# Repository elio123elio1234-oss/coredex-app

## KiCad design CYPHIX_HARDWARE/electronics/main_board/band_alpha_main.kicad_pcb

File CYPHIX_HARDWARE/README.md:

# CYPHIX_HARDWARE — Band α hardware design

The product hardware for **CYPHIX Band α**: the wearable 6-lead ECG strap with
dry electrodes that replaces the ESP32 + ADS1293 prototype. Requirements come
from the Band α specification (the bilingual artifact page,
`claude.ai/artifact/PpmwYJec8DWmWGM8rhy5re`).

The plan is built from the **product**: `system/product_tree.py` lists every deliverable, every
interface between two parts and every specification requirement with how it is proven, and its check
fails on an incomplete row. Risks are still tested in the cheapest way that can prove them, and the next
stage is paid for only after the previous one passes. (Until v0.16.0 the plan was built from risks alone,
and whole parts fell through it: the strap flex, the test plan, the board's fit in the housing.) The plan, with its live progress log, is the Hebrew page
published from `plan/plan.html`
(`claude.ai/artifact/PyT22bDzE1Ed9x9vdyoaew`).

## Stages

| # | Stage | Proves | Cost |
|---|---|---|---|
| 0 | On the computer | the design closes: size from the parts, schematic, parts available, everything fits in a solid model | none |
| 1 | Dry pads on the existing prototype | steel pads at the planned size give a readable ECG | about none |
| 2 | The new chip on the bench | the ADS129x family, the 4-channel plan and the existing apps work together | about none: the TI ADS1298 board is already owned |
| 3 | First wearable | miniature board, housing, strap and the flex inside it work on a wrist | being recomputed: the old $800–1,500 for five left out custom steel, sapphire, ceramic, the strap mould and the dock |
| 4 | Fixes and safety | safe and stable enough for a hospital study | $800–1,500 plus an accredited lab |

## Layout

```
CYPHIX_HARDWARE/
├── plan/          the plan page (plan.html + img/); publish plan.html to update the page
├── system/        product_tree.py: every deliverable, interface and requirement check (tree_html.py puts it on the plan page);
│                  budget.py → BUDGET.md: size, battery and mass, computed bottom-up from the parts
├── mechanical/    band_id.py = the industrial design model, concept v3.2 (render_v32.py + studio/ make its pictures,
│                  render_id.py the v3.1 ones; export_web_id.py feeds the page's 3D viewer); band_premium.py = the premium side variant P1, DROPPED by the owner
│                  2026-11-15 and off the page (code kept for reference only; its render/export scripts are not part of the page)
│                  (render_p.py, export_web_p.py); band_alpha.py = the first packaging check
├── electronics/   DESIGN_INTENT.md (the brief) + main_board/: schematic + 6-layer board rev 0.1 (make_schematic.py, make_pcb.py --route → KiCad 10 + Freerouting; DESIGN_NOTES.md, TEST_PLAN.md, bom.csv, PDF) + strap_flex/ (the RA flex); autorouted, not reviewed
├── firmware/      stage2_ads129x_xiao/: the bench firmware (XIAO nRF52840 + TI ADS1298 board)
├── experiments/   step-by-step protocols for the tests a person has to run
└── tools/         helper scripts
```

`HW_PLAYGROUND/` (the ADS1293 research area) stays as it is and is read-only
from here.

## Rules that are specific to this folder

- **No size is an input.** The render (35 × 26 × ~6 mm) and the spec's MEC-01
  (45 × 30 × 12 mm) were not derived from the parts. `system/budget.py` is the
  one place the module size comes from; the CAD model imports it.
- **The apps stay frozen at 320 Hz until the hardware is proven.** Stage 2
  firmware has a compatibility mode that streams the existing packet format, so
  no app change is needed to test new hardware. Moving the apps to 4 channels
  and 500 SPS is a `CYPHIX_SHARED` change and needs the owner's approval.
- **Patient safety is designed in from the first schematic**: patient current
  limited by series resistance, no recording while charging, battery-only
  operation whenever electrodes are on a person.
- **Nothing here has been measured until a stage says so.** A clean ERC/DRC, a
  collision-free model and a compiling firmware prove the design is
  well-formed, not that it works.
- A person with electronics experience reviews every board before it is ordered.
- **A stage starts only when the product tree has nothing `missing` or `conflict` that the stage needs**,
  and an independent reviewer (someone who did not write the design) has been through every file.

## Tools

- Python 3.12 in `.venv/` (`requirements.txt`): CadQuery for solids and STEP,
  PyVista for the pictures.
- KiCad 10 installed per user at
  `%LOCALAPPDATA%\Programs\KiCad\10.0` (`bin\kicad-cli.exe`).
- PlatformIO at `%USERPROFILE%\.platformio\penv\Scripts\pio.exe`.

<!-- v0.16.0 — the plan is built from the product tree (system/product_tree.py); stage-3 cost withdrawn; stage gate rule; earlier: what the folder is, its stages, layout (concept v3.2) and rules -->

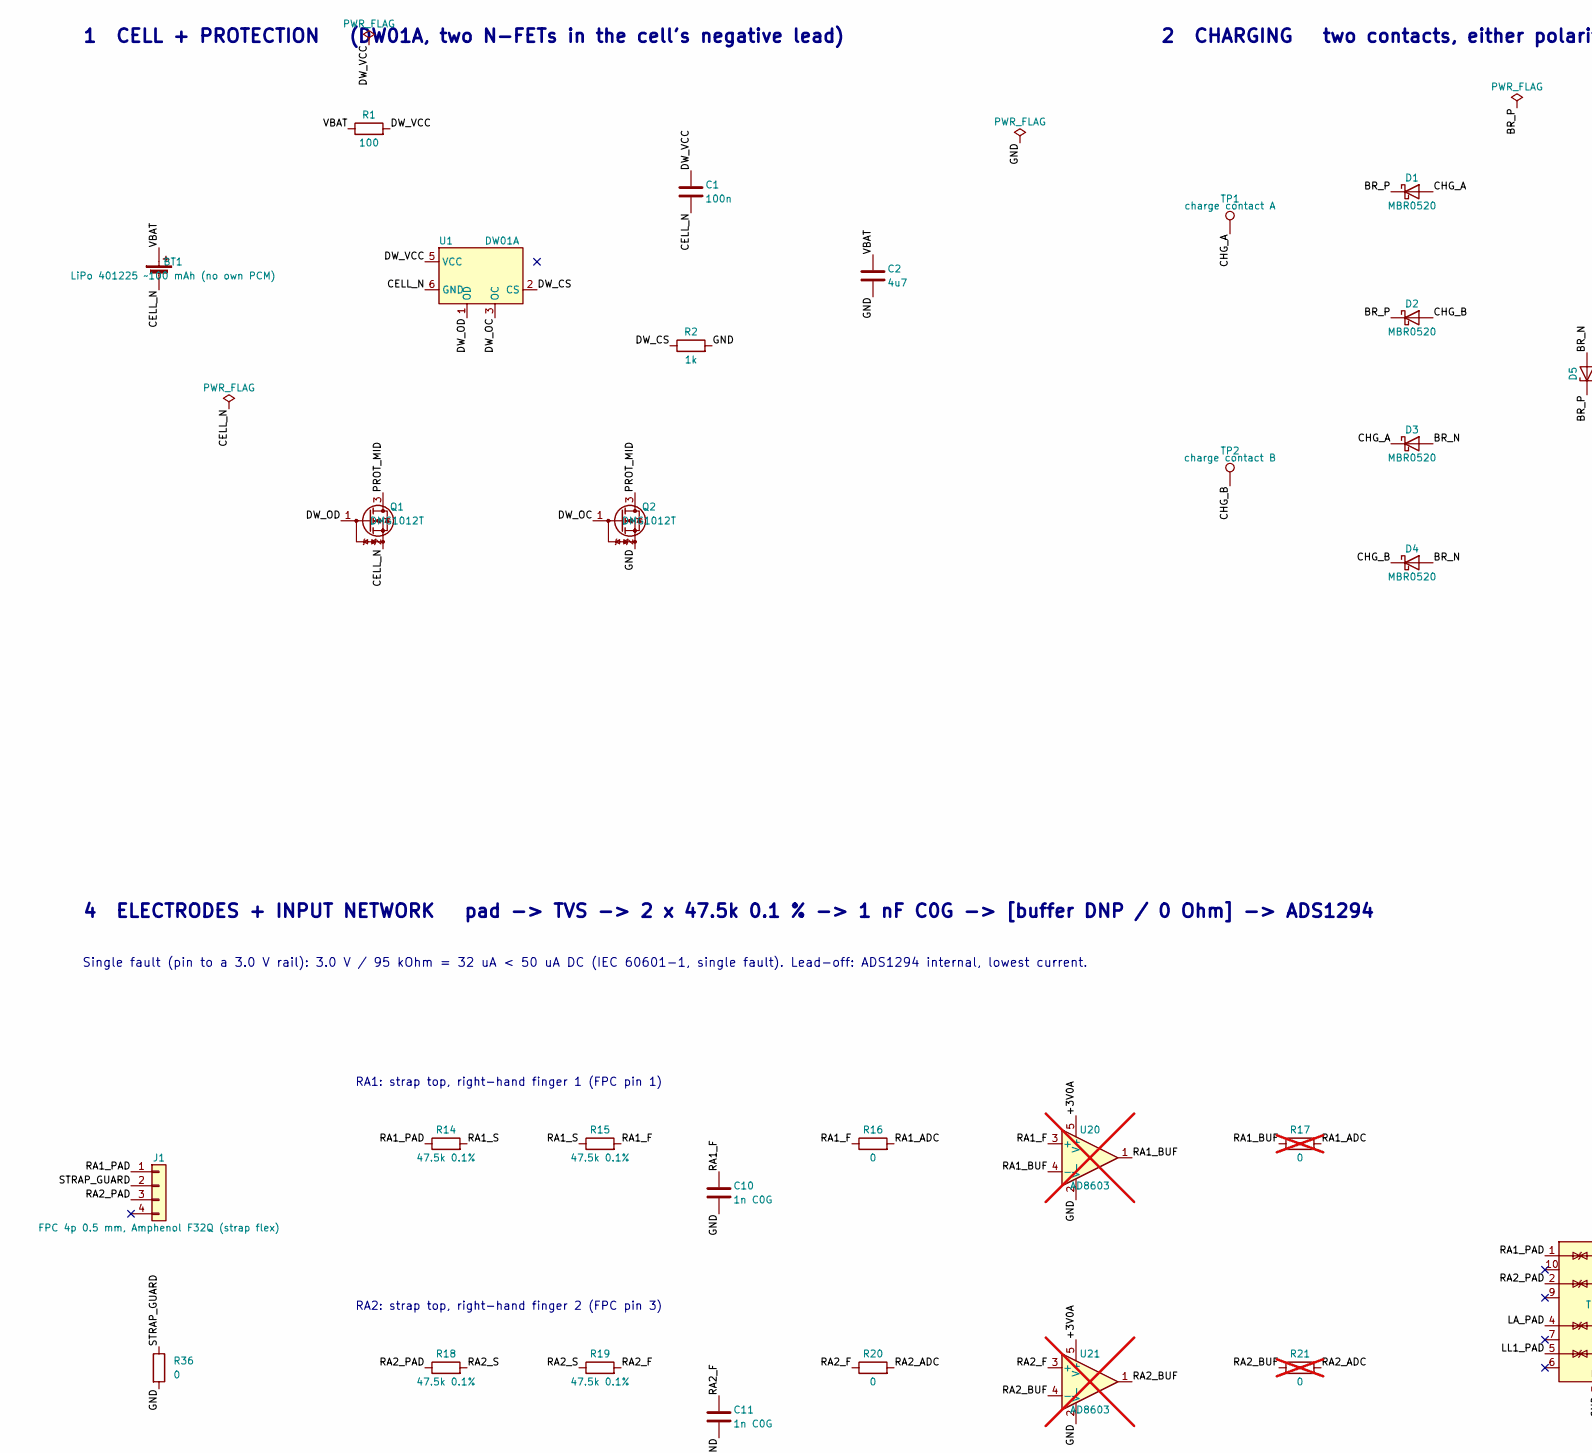
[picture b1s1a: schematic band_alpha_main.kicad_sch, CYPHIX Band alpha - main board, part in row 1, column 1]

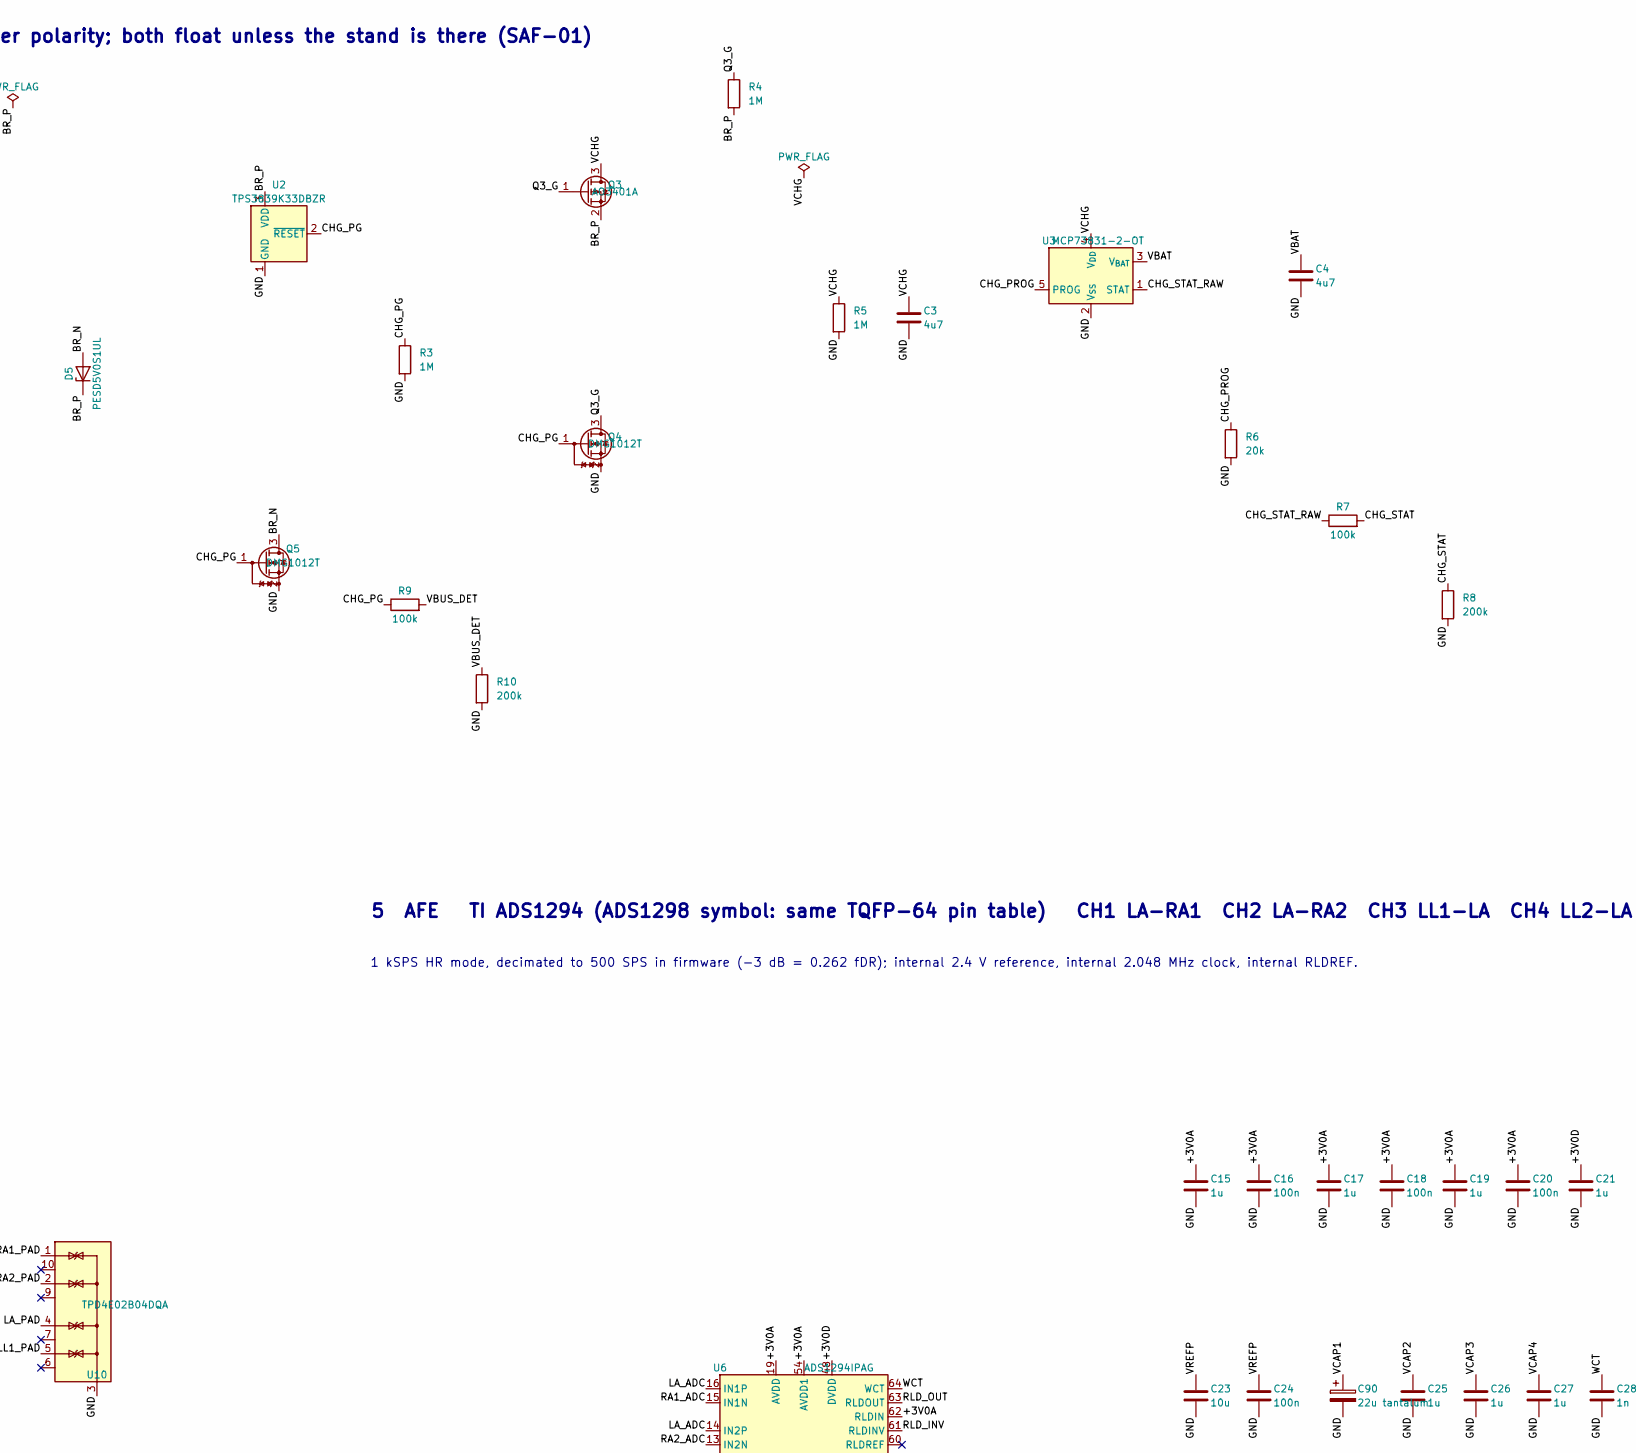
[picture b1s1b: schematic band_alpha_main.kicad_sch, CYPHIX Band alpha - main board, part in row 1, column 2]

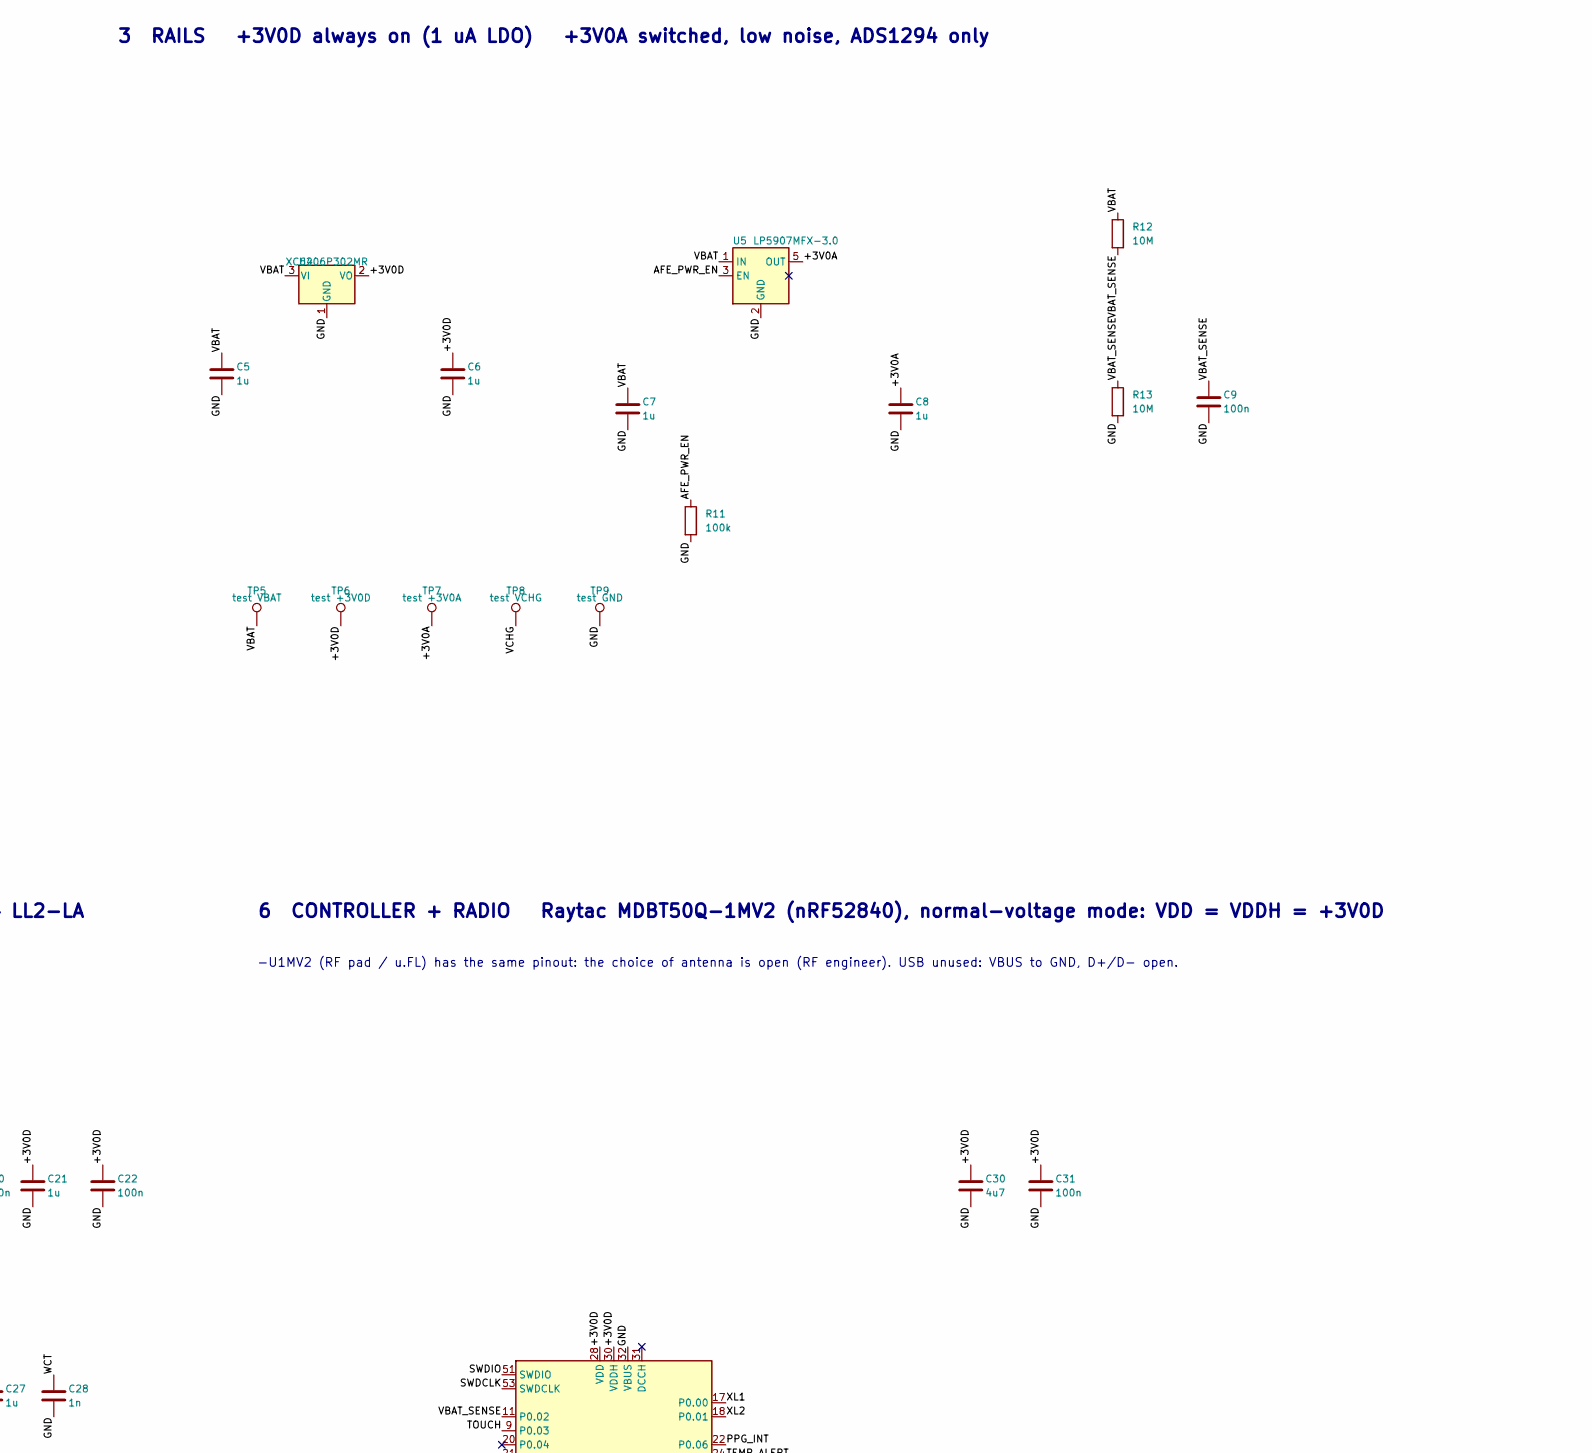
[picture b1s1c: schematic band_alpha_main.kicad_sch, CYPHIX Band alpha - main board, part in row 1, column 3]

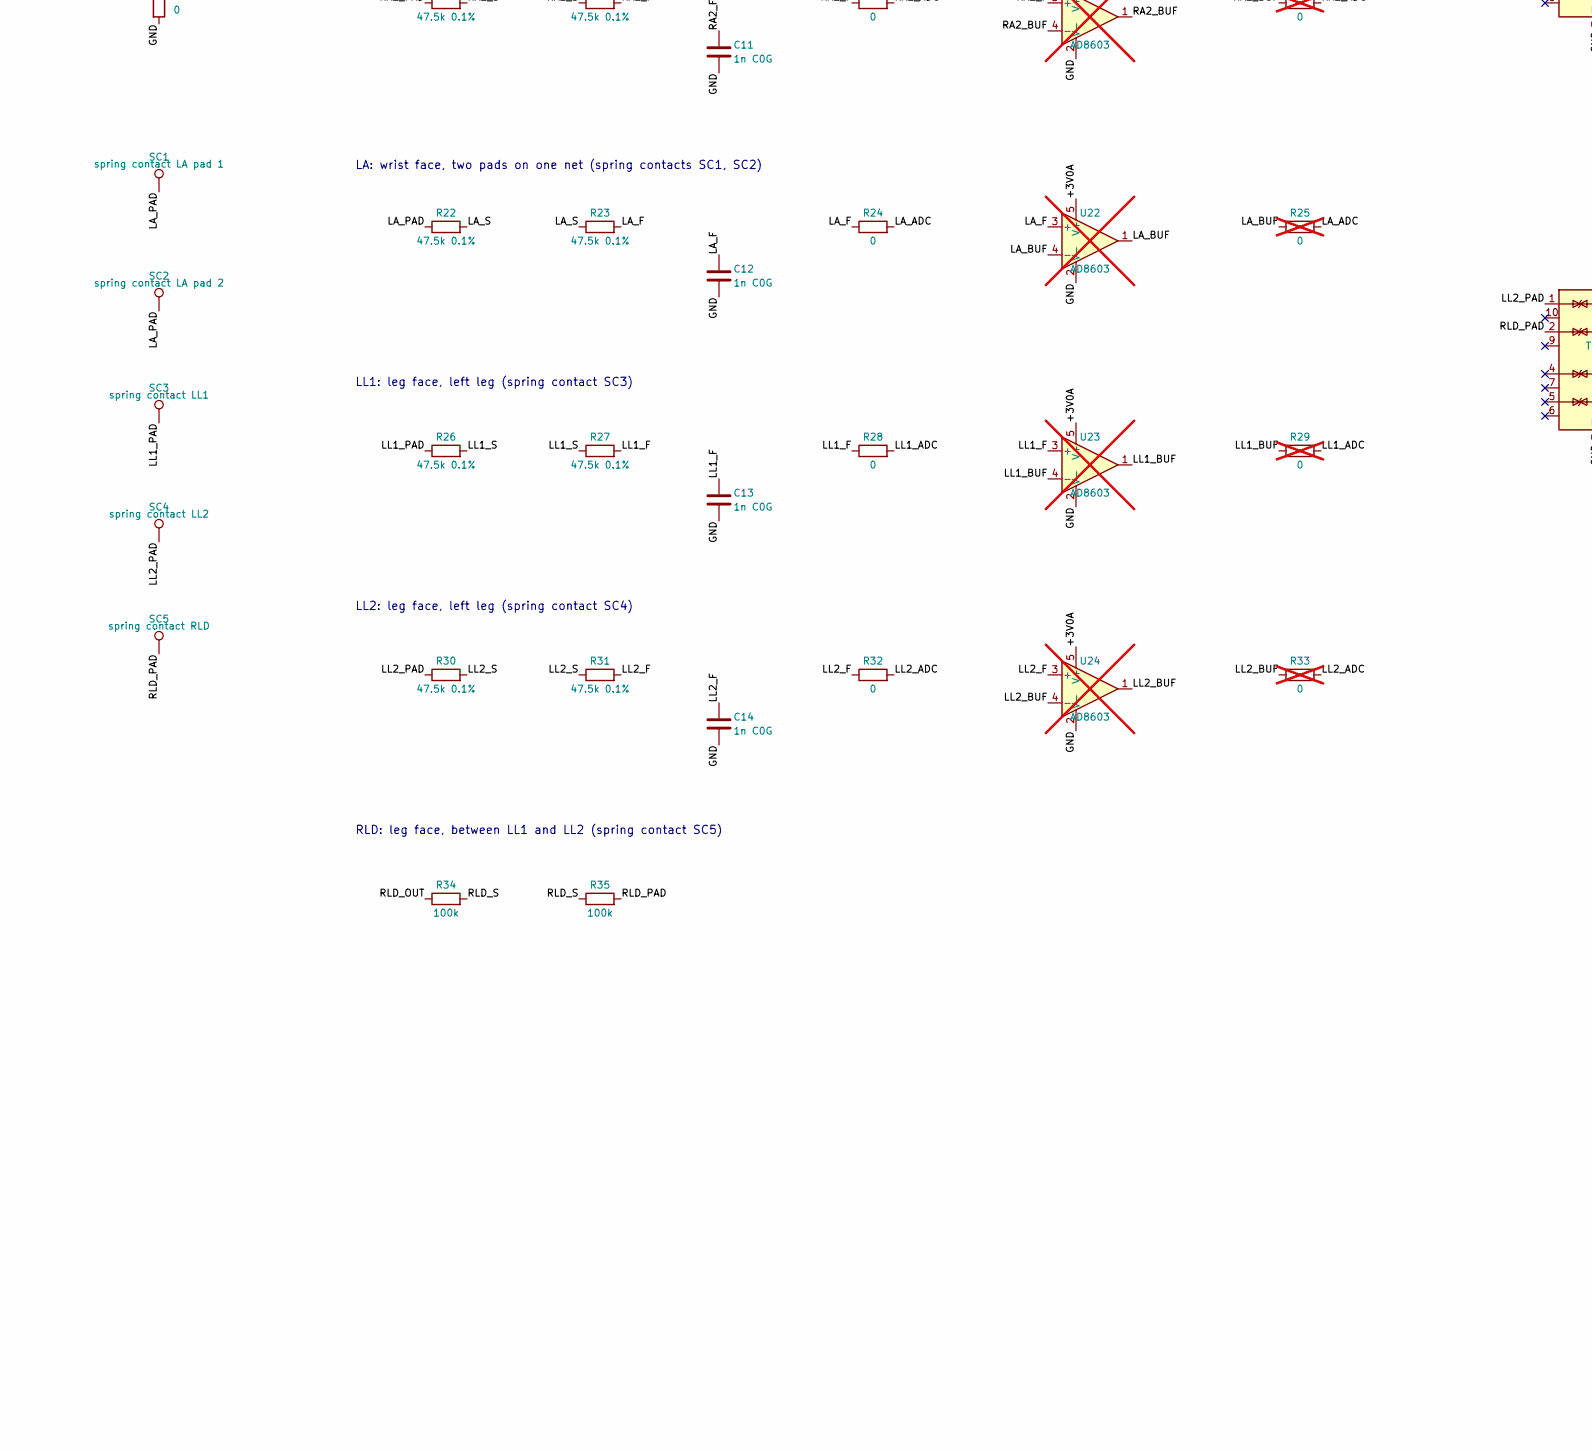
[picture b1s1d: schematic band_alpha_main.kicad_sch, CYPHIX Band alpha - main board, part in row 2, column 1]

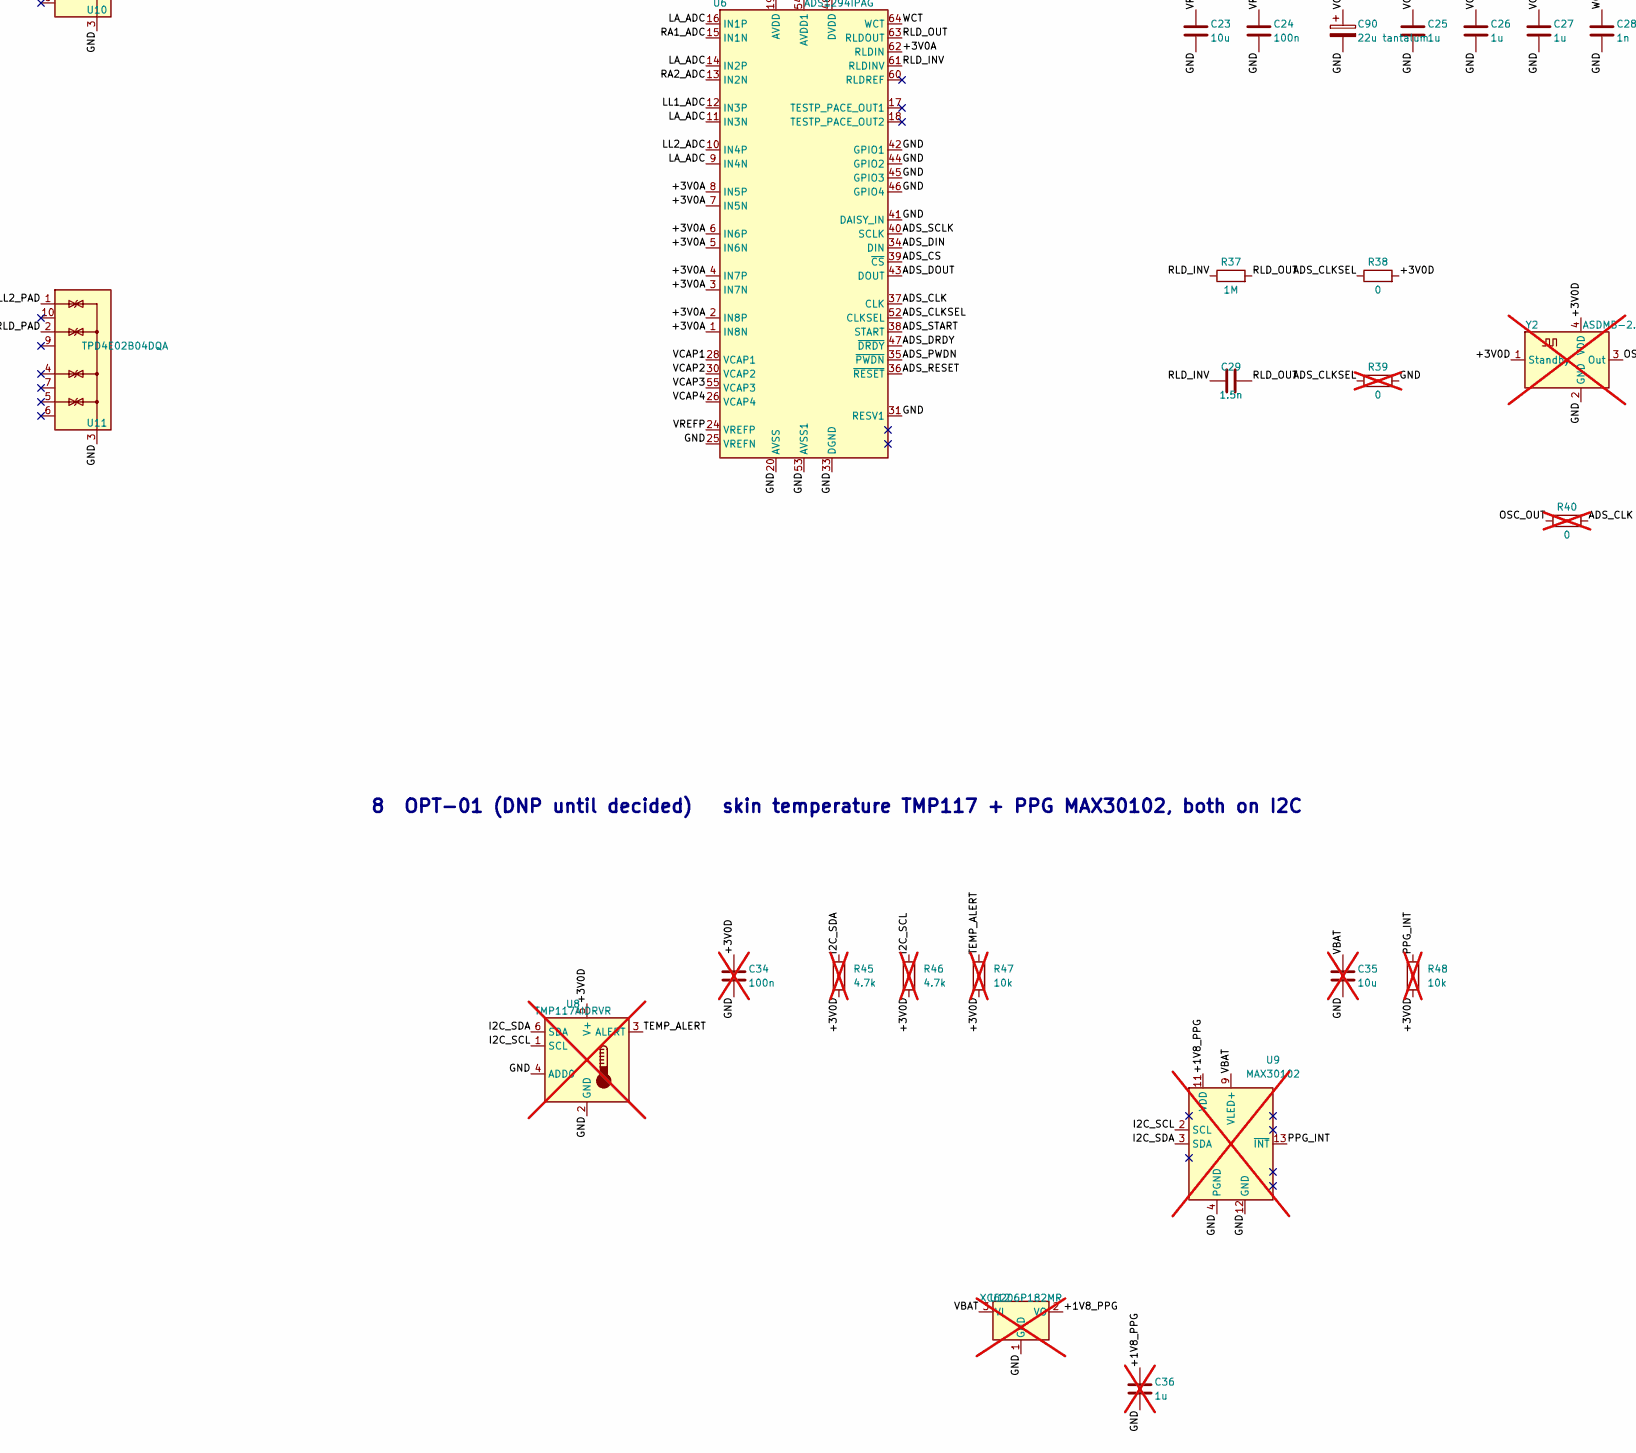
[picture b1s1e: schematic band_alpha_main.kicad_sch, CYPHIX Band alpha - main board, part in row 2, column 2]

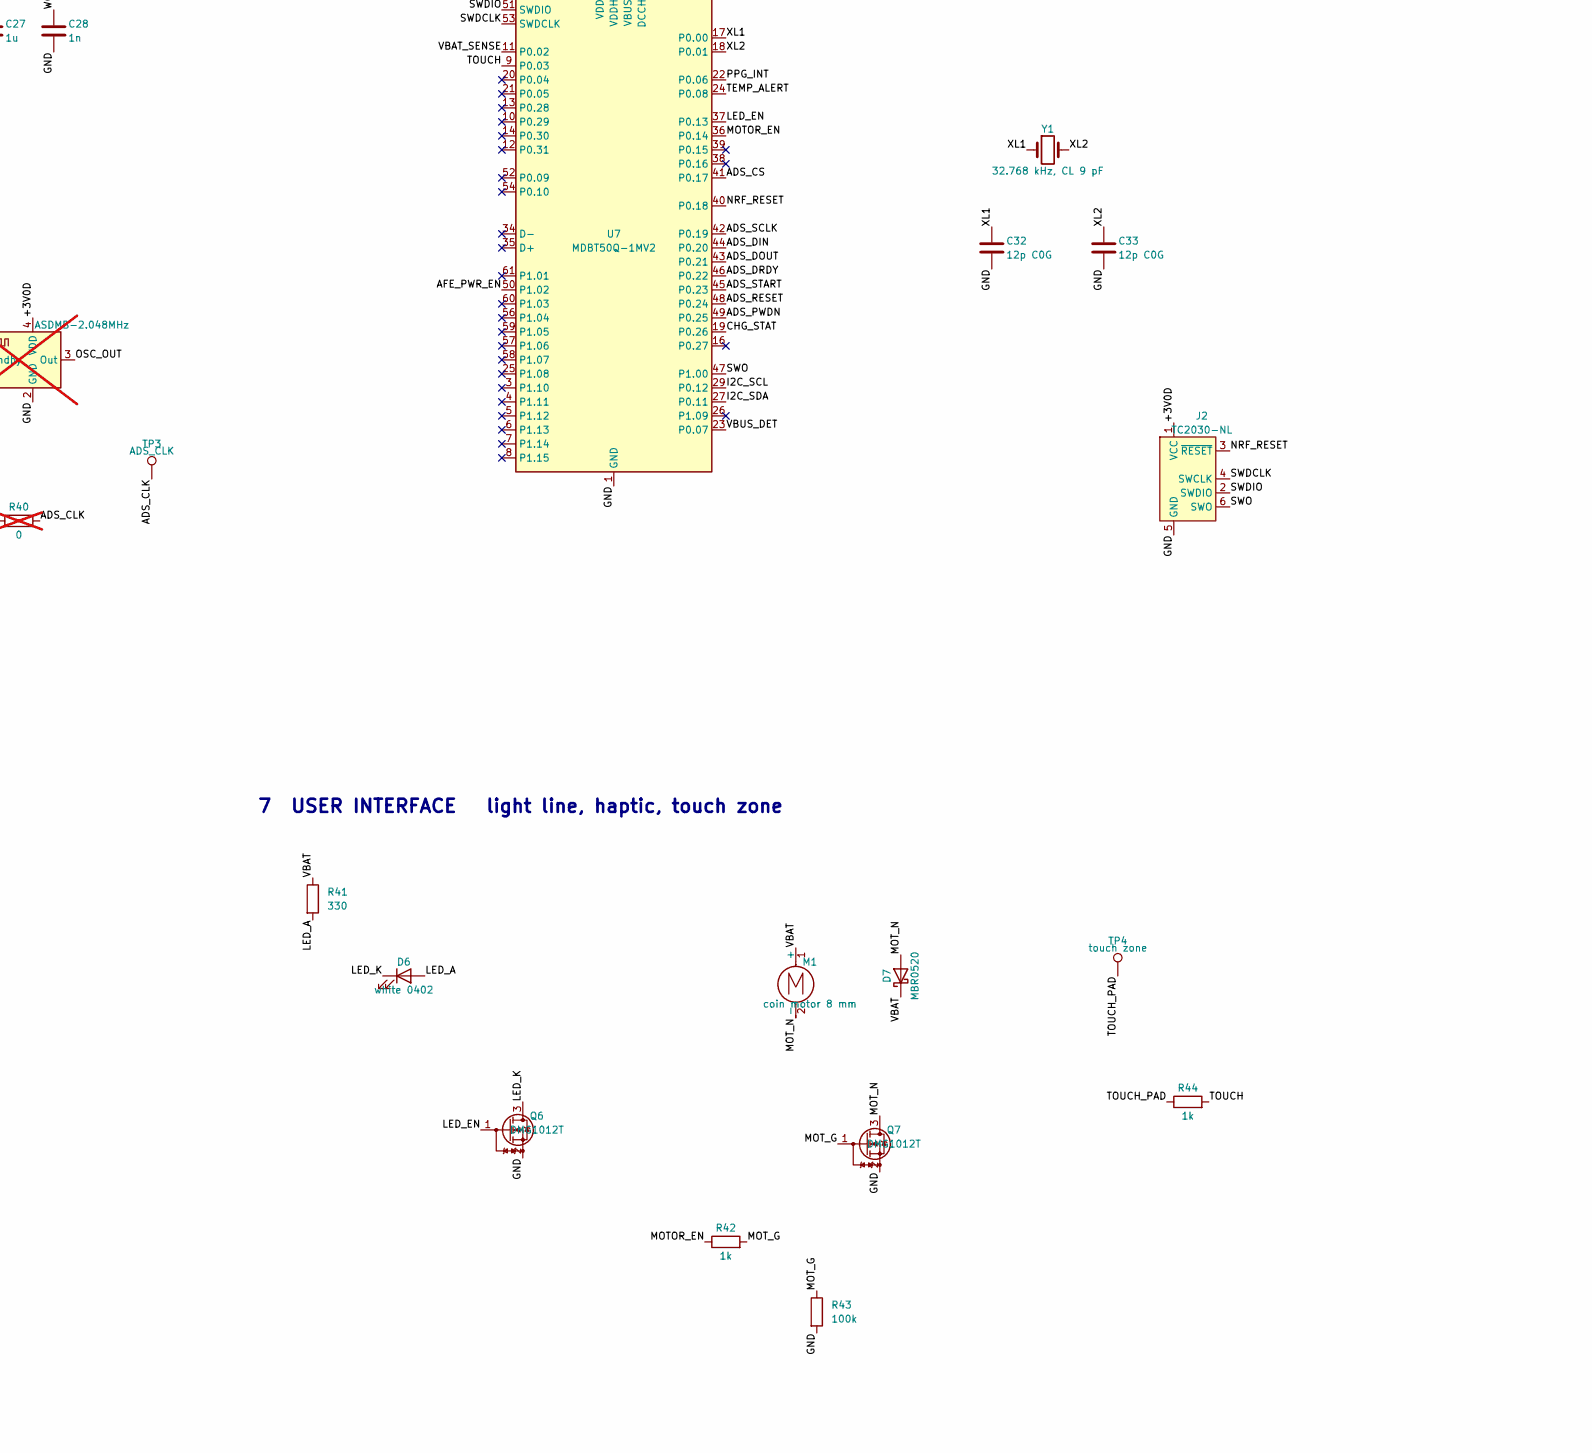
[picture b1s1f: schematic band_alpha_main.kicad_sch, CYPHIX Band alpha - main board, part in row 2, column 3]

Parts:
BT1: LiPo 401225 ~100 mAh (no own PCM); Cell_Tabs_2x
C1, C9, C16, C18, C20, C22, C24, C31: 100n; C_0402_1005Metric
C2, C3, C4, C30: 4u7; C_0603_1608Metric
C5, C6, C7, C8, C15, C17, C19, C21, C25, C26, C27: 1u; C_0402_1005Metric
C10, C11, C12, C13, C14: 1n C0G; C_0402_1005Metric
C23: 10u; C_0603_1608Metric
C28: 1n; C_0402_1005Metric
C29: 1.5n; C_0402_1005Metric
C32, C33: 12p C0G; C_0402_1005Metric
C34: 100n; C_0402_1005Metric; not fitted
C35: 10u; C_0603_1608Metric; not fitted
C36: 1u; C_0402_1005Metric; not fitted
C90: 22u tantalum; CP_EIA-2012-12_Kemet-R
D1, D2, D3, D4, D7: MBR0520; D_SOD-123
D5: PESD5V0S1UL; D_SOD-882
D6: white 0402; LED_0402_1005Metric
J1: FPC 4p 0.5 mm, Amphenol F32Q (strap flex); Amphenol_F32Q-1A7x1-11004_1x04-1MP_P0.5mm_Horizontal
J2: TC2030-NL; Tag-Connect_TC2030-IDC-NL_2x03_P1.27mm_Vertical
M1: coin motor 8 mm; Motor_Pads_2x
Q1, Q2, Q4, Q5, Q6, Q7: DMG1012T; SOT-523
Q3: AO3401A; SOT-23
R1: 100; R_0402_1005Metric
R2, R42, R44: 1k; R_0402_1005Metric
R3, R4, R5, R37: 1M; R_0402_1005Metric
R6: 20k; R_0402_1005Metric
R7, R9, R11, R34, R35, R43: 100k; R_0402_1005Metric
R8, R10: 200k; R_0402_1005Metric
R12, R13: 10M; R_0402_1005Metric
R14, R15, R18, R19, R22, R23, R26, R27, R30, R31: 47.5k 0.1%; R_0402_1005Metric
R16, R20, R24, R28, R32, R36, R38: 0; R_0402_1005Metric
R17, R21, R25, R29, R33, R39, R40: 0; R_0402_1005Metric; not fitted
R41: 330; R_0402_1005Metric
R45, R46: 4.7k; R_0402_1005Metric; not fitted
R47, R48: 10k; R_0402_1005Metric; not fitted
SC1: spring contact LA pad 1; TestPoint_Pad_1.5x1.5mm
SC2: spring contact LA pad 2; TestPoint_Pad_1.5x1.5mm
SC3: spring contact LL1; TestPoint_Pad_1.5x1.5mm
SC4: spring contact LL2; TestPoint_Pad_1.5x1.5mm
SC5: spring contact RLD; TestPoint_Pad_1.5x1.5mm
TP1: charge contact A; TestPoint_Pad_D2.0mm
TP2: charge contact B; TestPoint_Pad_D2.0mm
TP3: ADS_CLK; TestPoint_Pad_D1.0mm
TP4: touch zone; TestPoint_Pad_2.0x2.0mm
TP5: test VBAT; TestPoint_Pad_D1.0mm
TP6: test +3V0D; TestPoint_Pad_D1.0mm
TP7: test +3V0A; TestPoint_Pad_D1.0mm
TP8: test VCHG; TestPoint_Pad_D1.0mm
TP9: test GND; TestPoint_Pad_D1.0mm
U1: DW01A; SOT-23-6
U2: TPS3839K33DBZR; SOT-23
U3: MCP73831-2-OT; SOT-23-5
U4: XC6206P302MR; SOT-23-3
U5: LP5907MFX-3.0; SOT-23-5
U6: ADS1294IPAG; TQFP-64_10x10mm_P0.5mm
U7: MDBT50Q-1MV2; Raytac_MDBT50Q
U8: TMP117AIDRVR; WSON-6-1EP_2x2mm_P0.65mm_EP1x1.6mm; not fitted
U9: MAX30102; Maxim_OLGA-14_3.3x5.6mm_P0.8mm; not fitted
U10, U11: TPD4E02B04DQA; USON-10_2.5x1.0mm_P0.5mm
U12: XC6206P182MR; SOT-23-3; not fitted
U20, U21, U22, U23, U24: AD8603; TSOT-23-5; not fitted
Y1: 32.768 kHz, CL 9 pF; Crystal_SMD_2012-2Pin_2.0x1.2mm
Y2: ASDMB-2.048MHz; Oscillator_SMD_Abracon_ASDMB-4Pin_2.5x2.0mm; not fitted

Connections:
/+1V8_PPG: C36.1, U9.11 (VDD), U12.2 (VO)
/+3V0A: C8.1, C15.1, C16.1, C17.1, C18.1, C19.1, C20.1, TP7.1, U5.5 (OUT), U6.1 (IN8N), U6.2 (IN8P), U6.3 (IN7N), U6.4 (IN7P), U6.5 (IN6N), U6.6 (IN6P), U6.7 (IN5N), U6.8 (IN5P), U6.19 (AVDD), U6.21 (AVDD), U6.22 (AVDD), U6.54 (AVDD1), U6.56 (AVDD), U6.59 (AVDD), U6.62 (RLDIN), U20.5 (V+), U21.5 (V+), U22.5 (V+), U23.5 (V+), U24.5 (V+)
/+3V0D: C6.1, C21.1, C22.1, C30.1, C31.1, C34.1, J2.1 (VCC), R38.2, R45.2, R46.2, R47.2, R48.2, TP6.1, U4.2 (VO), U6.48 (DVDD), U6.50 (DVDD), U7.28 (VDD), U7.30 (VDDH), U8.5 (V+), Y2.1 (Standby), Y2.4 (VDD)
/ADS_CLK: R40.2, TP3.1, U6.37 (CLK)
/ADS_CLKSEL: R38.1, R39.1, U6.52 (CLKSEL)
/ADS_CS: U6.39 (~CS), U7.41 (P0.17)
/ADS_DIN: U6.34 (DIN), U7.44 (P0.20)
/ADS_DOUT: U6.43 (DOUT), U7.43 (P0.21)
/ADS_DRDY: U6.47 (~DRDY), U7.46 (P0.22)
/ADS_PWDN: U6.35 (~PWDN), U7.49 (P0.25)
/ADS_RESET: U6.36 (~RESET), U7.48 (P0.24)
/ADS_SCLK: U6.40 (SCLK), U7.42 (P0.19)
/ADS_START: U6.38 (START), U7.45 (P0.23)
/AFE_PWR_EN: R11.1, U5.3 (EN), U7.50 (P1.02)
/BR_N: D3.2 (A), D4.2 (A), D5.2 (A), Q5.3 (D)
/BR_P: D1.1 (K), D2.1 (K), D5.1 (K), Q3.2 (S), R4.2, U2.3 (VDD)
/CELL_N: BT1.2 (-), C1.2, Q1.2 (S), U1.6 (GND)
/CHG_A: D1.2 (A), D3.1 (K), TP1.1
/CHG_B: D2.2 (A), D4.1 (K), TP2.1
/CHG_PG: Q4.1 (G), Q5.1 (G), R3.1, R9.1, U2.2 (~RESET)
/CHG_PROG: R6.1, U3.5 (PROG)
/CHG_STAT: R7.2, R8.1, U7.19 (P0.26)
/CHG_STAT_RAW: R7.1, U3.1 (STAT)
/DW_CS: R2.1, U1.2 (CS)
/DW_OC: Q2.1 (G), U1.3 (OC)
/DW_OD: Q1.1 (G), U1.1 (OD)
/DW_VCC: C1.1, R1.2, U1.5 (VCC)
/GND: C2.2, C3.2, C4.2, C5.2, C6.2, C7.2, C8.2, C9.2, C10.2, C11.2, C12.2, C13.2, C14.2, C15.2, C16.2, C17.2, C18.2, C19.2, C20.2, C21.2, C22.2, C23.2, C24.2, C25.2, C26.2, C27.2, C28.2, C30.2, C31.2, C32.2, C33.2, C34.2, C35.2, C36.2, C90.2, J2.5 (GND), Q2.2 (S), Q4.2 (S), Q5.2 (S), Q6.2 (S), Q7.2 (S), R2.2, R3.2, R5.2, R6.2, R8.2, R10.2, R11.2, R13.2, R36.2, R39.2, R43.2, TP9.1, U2.1 (GND), U3.2 (V_{SS}), U4.1 (GND), U5.2 (GND), U6.20 (AVSS), U6.23 (AVSS), U6.25 (VREFN), U6.31 (RESV1), U6.32 (AVSS), U6.33 (DGND), U6.41 (DAISY_IN), U6.42 (GPIO1), U6.44 (GPIO2), U6.45 (GPIO3), U6.46 (GPIO4), U6.49 (DGND), U6.51 (DGND), U6.53 (AVSS1), U6.57 (AVSS), U6.58 (AVSS), U7.1 (GND), U7.2 (GND), U7.15 (GND), U7.32 (VBUS), U7.33 (GND), U7.55 (GND), U8.2 (GND), U8.4 (ADD0), U9.4 (PGND), U9.12 (GND), U10.3 (G), U10.8 (G), U11.3 (G), U11.8 (G), U12.1 (GND), U20.2 (V-), U21.2 (V-), U22.2 (V-), U23.2 (V-), U24.2 (V-), Y2.2 (GND)
/I2C_SCL: R46.1, U7.29 (P0.12), U8.1 (SCL), U9.2 (SCL)
/I2C_SDA: R45.1, U7.27 (P0.11), U8.6 (SDA), U9.3 (SDA)
/LA_ADC: R24.2, R25.2, U6.9 (IN4N), U6.11 (IN3N), U6.14 (IN2P), U6.16 (IN1P)
/LA_BUF: R25.1, U22.1, U22.4 (-)
/LA_F: C12.1, R23.2, R24.1, U22.3 (+)
/LA_PAD: R22.1, SC1.1, SC2.1, U10.4 (IO3)
/LA_S: R22.2, R23.1
/LED_A: D6.2 (A), R41.2
/LED_EN: Q6.1 (G), U7.37 (P0.13)
/LED_K: D6.1 (K), Q6.3 (D)
/LL1_ADC: R28.2, R29.2, U6.12 (IN3P)
/LL1_BUF: R29.1, U23.1, U23.4 (-)
/LL1_F: C13.1, R27.2, R28.1, U23.3 (+)
/LL1_PAD: R26.1, SC3.1, U10.5 (IO4)
/LL1_S: R26.2, R27.1
/LL2_ADC: R32.2, R33.2, U6.10 (IN4P)
/LL2_BUF: R33.1, U24.1, U24.4 (-)
/LL2_F: C14.1, R31.2, R32.1, U24.3 (+)
/LL2_PAD: R30.1, SC4.1, U11.1 (IO1)
/LL2_S: R30.2, R31.1
/MOTOR_EN: R42.1, U7.36 (P0.14)
/MOT_G: Q7.1 (G), R42.2, R43.1
/MOT_N: D7.2 (A), M1.2 (-), Q7.3 (D)
/NRF_RESET: J2.3 (~RESET), U7.40 (P0.18)
/OSC_OUT: R40.1, Y2.3 (Out)
/PPG_INT: R48.1, U7.22 (P0.06), U9.13 (~INT)
/PROT_MID: Q1.3 (D), Q2.3 (D)
/Q3_G: Q3.1 (G), Q4.3 (D), R4.1
/RA1_ADC: R16.2, R17.2, U6.15 (IN1N)
/RA1_BUF: R17.1, U20.1, U20.4 (-)
/RA1_F: C10.1, R15.2, R16.1, U20.3 (+)
/RA1_PAD: J1.1, R14.1, U10.1 (IO1)
/RA1_S: R14.2, R15.1
/RA2_ADC: R20.2, R21.2, U6.13 (IN2N)
/RA2_BUF: R21.1, U21.1, U21.4 (-)
/RA2_F: C11.1, R19.2, R20.1, U21.3 (+)
/RA2_PAD: J1.3, R18.1, U10.2 (IO2)
/RA2_S: R18.2, R19.1
/RLD_INV: C29.1, R37.1, U6.61 (RLDINV)
/RLD_OUT: C29.2, R34.1, R37.2, U6.63 (RLDOUT)
/RLD_PAD: R35.2, SC5.1, U11.2 (IO2)
/RLD_S: R34.2, R35.1
/STRAP_GUARD: J1.2, R36.1
/SWDCLK: J2.4 (SWCLK), U7.53 (SWDCLK)
/SWDIO: J2.2 (SWDIO), U7.51 (SWDIO)
/SWO: J2.6 (SWO), U7.47 (P1.00)
/TEMP_ALERT: R47.1, U7.24 (P0.08), U8.3 (ALERT)
/TOUCH: R44.2, U7.9 (P0.03)
/TOUCH_PAD: R44.1, TP4.1
/VBAT: BT1.1 (+), C2.1, C4.1, C5.1, C7.1, C35.1, D7.1 (K), M1.1 (+), R1.1, R12.1, R41.1, TP5.1, U3.3 (V_{BAT}), U4.3 (VI), U5.1 (IN), U9.9 (VLED+), U9.10 (VLED+), U12.3 (VI)
/VBAT_SENSE: C9.1, R12.2, R13.1, U7.11 (P0.02)
/VBUS_DET: R9.2, R10.1, U7.23 (P0.07)
/VCAP1: C90.1, U6.28 (VCAP1)
/VCAP2: C25.1, U6.30 (VCAP2)
/VCAP3: C26.1, U6.55 (VCAP3)
/VCAP4: C27.1, U6.26 (VCAP4)
/VCHG: C3.1, Q3.3 (D), R5.1, TP8.1, U3.4 (V_{DD})
/VREFP: C23.1, C24.1, U6.24 (VREFP)
/WCT: C28.1, U6.64 (WCT)
/XL1: C32.1, U7.17 (P0.00), Y1.1
/XL2: C33.1, U7.18 (P0.01), Y1.2

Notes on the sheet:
1 CELL + PROTECTION (DW01A, two N-FETs in the cell's negative lead)
2 CHARGING two contacts, either polarity; both float unless the stand is there (SAF-01)
3 RAILS +3V0D always on (1 uA LDO) +3V0A switched, low noise, ADS1294 only
4 ELECTRODES + INPUT NETWORK pad -> TVS -> 2 x 47.5k 0.1 % -> 1 nF C0G -> [buffer DNP / 0 Ohm] -> ADS1294
Single fault (pin to a 3.0 V rail): 3.0 V / 95 kOhm = 32 uA < 50 uA DC (IEC 60601-1, single fault). Lead-off: ADS1294 internal, lowest current.
RA1: strap top, right-hand finger 1 (FPC pin 1)
RA2: strap top, right-hand finger 2 (FPC pin 3)
LA: wrist face, two pads on one net (spring contacts SC1, SC2)
LL1: leg face, left leg (spring contact SC3)
LL2: leg face, left leg (spring contact SC4)
RLD: leg face, between LL1 and LL2 (spring contact SC5)
5 AFE TI ADS1294 (ADS1298 symbol: same TQFP-64 pin table) CH1 LA-RA1 CH2 LA-RA2 CH3 LL1-LA CH4 LL2-LA
1 kSPS HR mode, decimated to 500 SPS in firmware (-3 dB = 0.262 fDR); internal 2.4 V reference, internal 2.048 MHz clock, internal RLDREF.
6 CONTROLLER + RADIO Raytac MDBT50Q-1MV2 (nRF52840), normal-voltage mode: VDD = VDDH = +3V0D
-U1MV2 (RF pad / u.FL) has the same pinout: the choice of antenna is open (RF engineer). USB unused: VBUS to GND, D+/D- open.
7 USER INTERFACE light line, haptic, touch zone
8 OPT-01 (DNP until decided) skin temperature TMP117 + PPG MAX30102, both on I2C
